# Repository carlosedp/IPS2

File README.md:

# IPS2

The infamous interruptible power supply is back version 2 with usbC and more mmpfh (700mA@12V / 500mA@-12V).

IPS is a 2HP opensource (cc-by-sa-nc) eurorack module. It’s a switched-mode power supply that converts the 5V power from any USB type C interface/charger into +12V/-12V for your modular synthesizer. This does not allow you to power big racks but can easily power up small to medium size systems (check powerconsumption with f.e. modulargrid.net)
You can also use the unit without frontpanel inside a case (no access to the SHUT inputs) if it has a power switch and a 5V input.

Unlike IPS1 this module is built around a monolytic IC which houses two independent regulators, the TPS65131 from TI. It still has the infamous shutdown inputs for the regulators, which are accessible thru two jacks on the frontpanel.
Quote from IPS1: “This gives you a very different approach to operate a connected module. By “proper” modulation of it’s own powersupply voltages any connected module(s) can operate then in a, let’s say:  “near death state”, which can create interesting effects.

DISCLAIMER:
The shutdown inputs are a very experimental feature for those who like to experiment on their own risk with reduced or chopped supply voltages for their modules/setup. We take no responibility for damage or the like. (should not occur, cause no inversion of voltage is possible, only reduction of voltage is possible)

In a glimpse:

- modern and fast 1.25MHz switching regulator from Texas Instruments deliver up to 700mA@12V and 500mA@-12V
- IPS mainboard can be mounted inside a case without frontpanel like a common PSU (flatmount, has 2nd location for USB C connector and also pads for wires)
- cheap – can be used with any USB type C charger
- it’s friggin tiny

In this fork, I've replaced the USB connectors to some more available on JLCPCB.

Also I've added a front-panel design that is connected to the PCB with break-tabs so they can
be easily manufactured in one run and separated. Components also have JLCPCB part numbers.

I/O:

- SHUT +12V deactivates the swiching regulator for the positive rail
- SHUT -12V deactivates the switching regulator for the negative rail
- internal 10 pin molex output header

Power Output:

- +12V 700mA / -12V 500mA (if incoming USB interface delivers it)

Dimensions:

- Width: 2 HP (10mm)
- Depth: 13mm

## License

CC-BY-SA-NC license

by seismic industries / 2019

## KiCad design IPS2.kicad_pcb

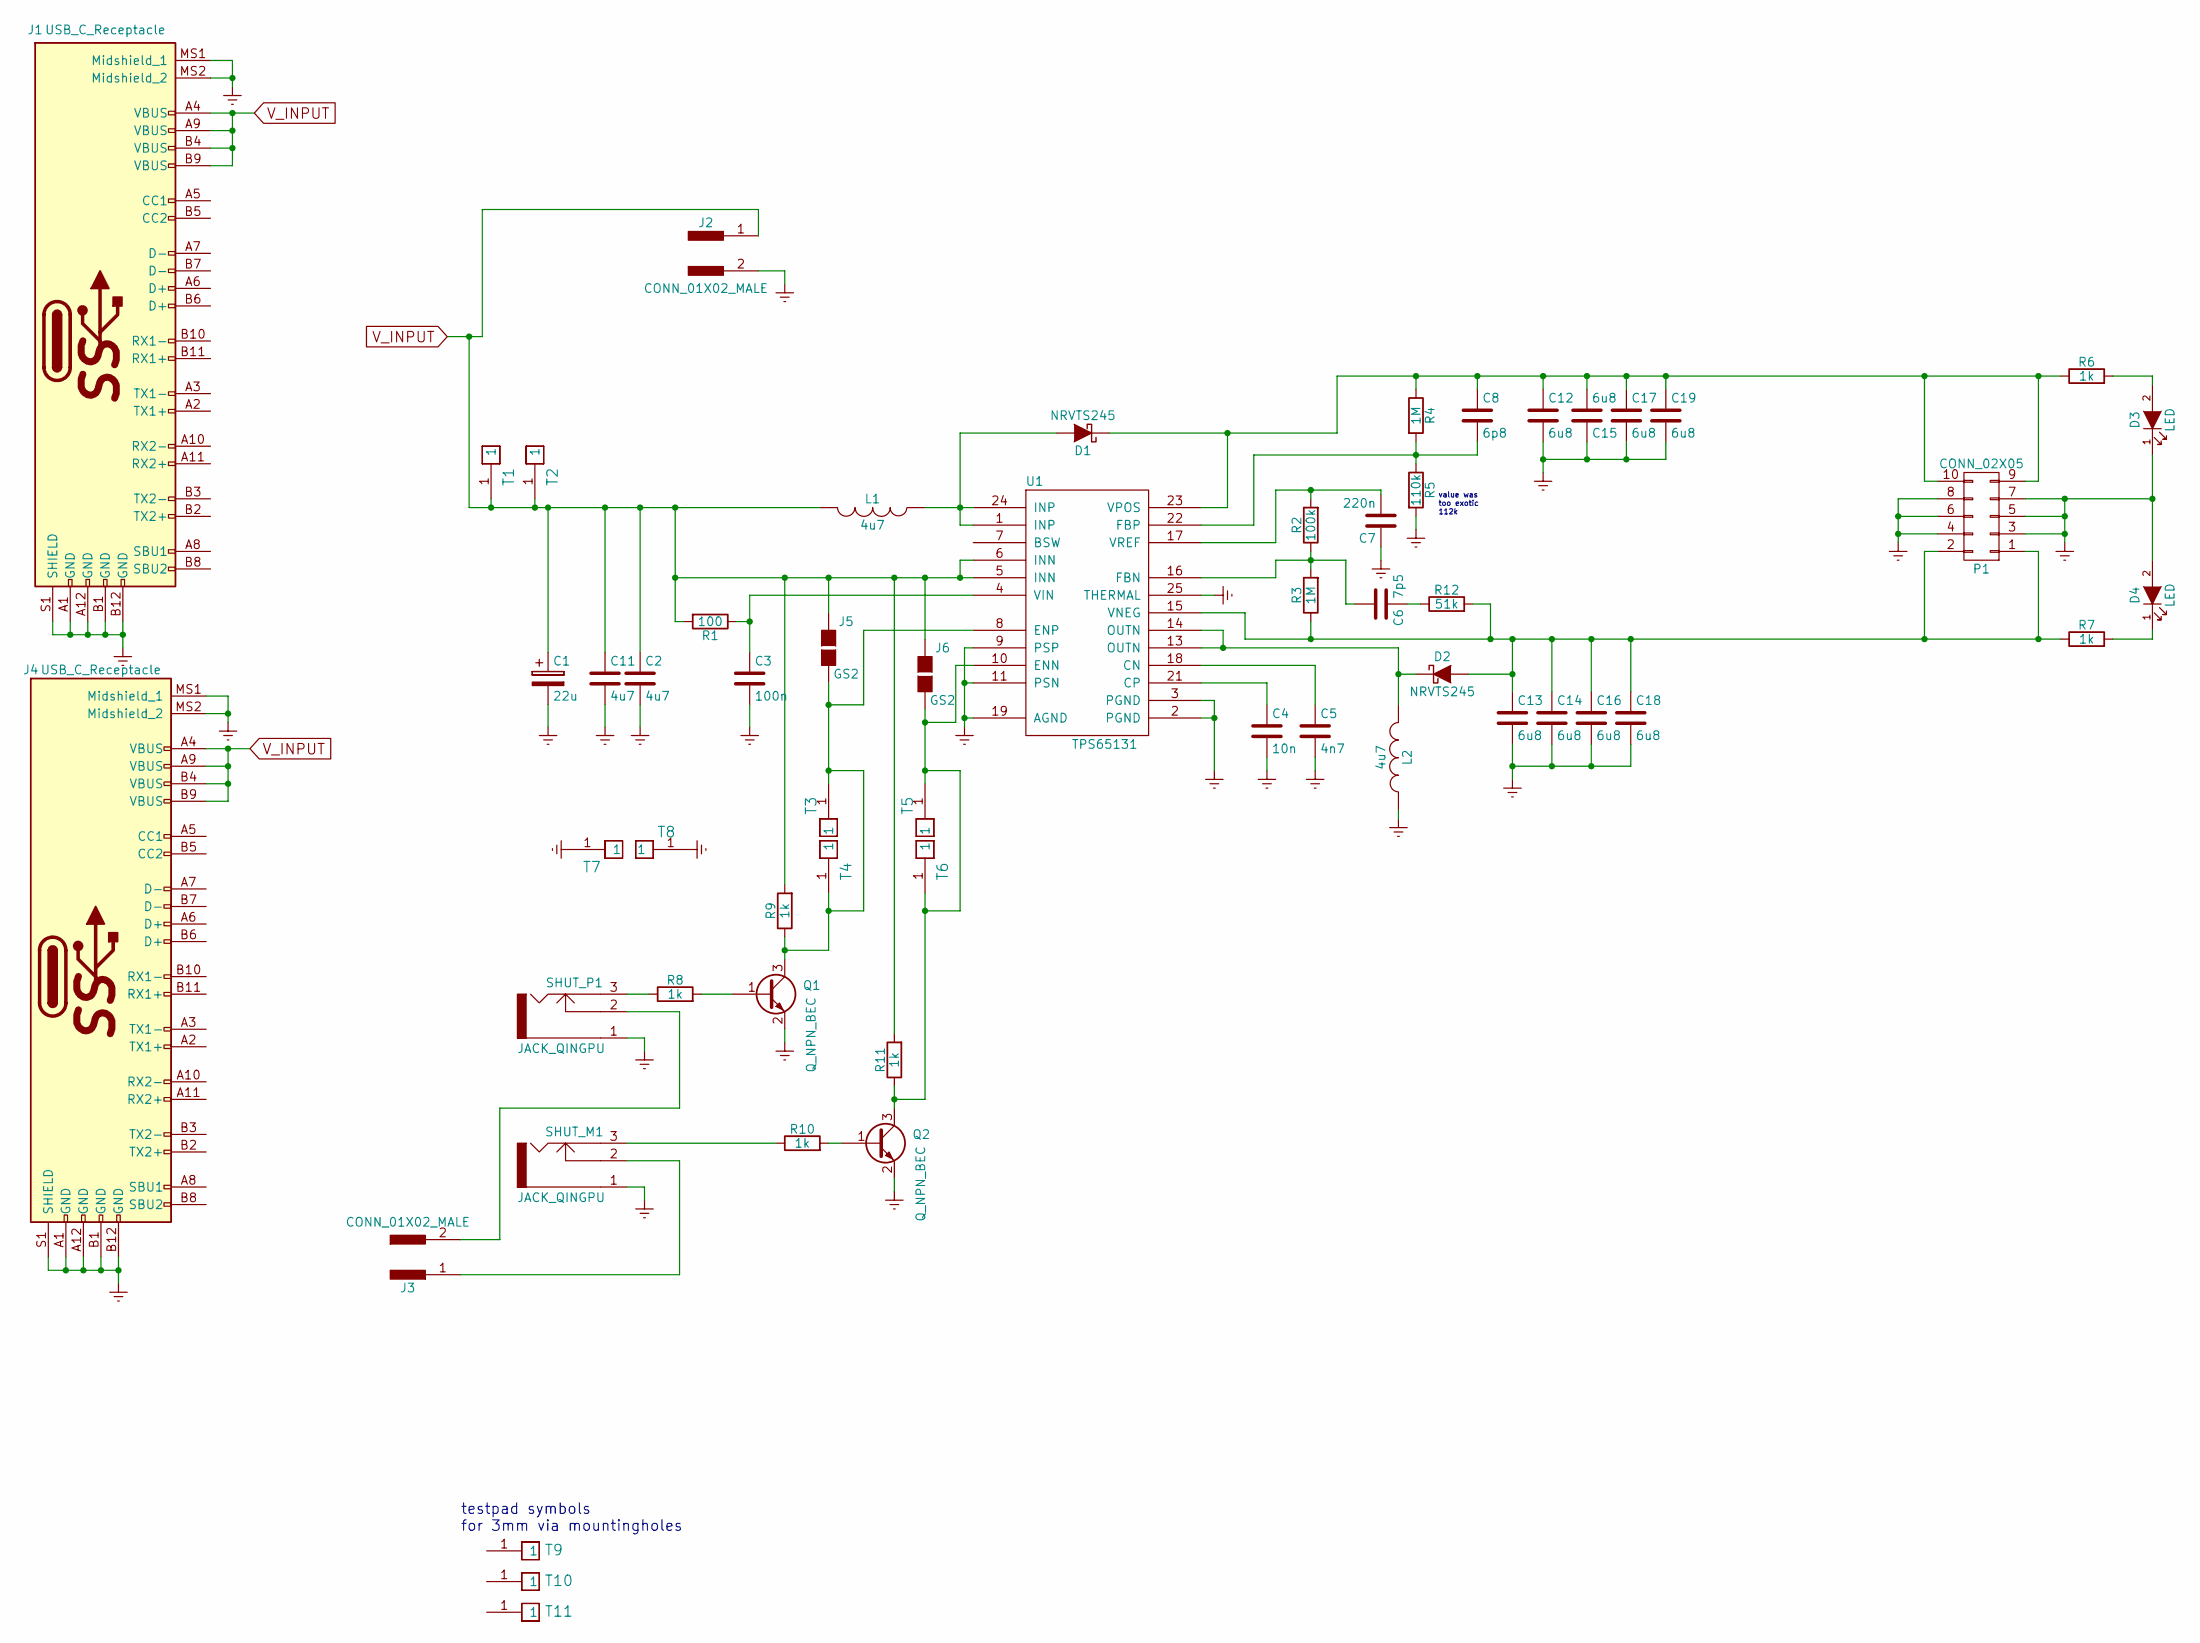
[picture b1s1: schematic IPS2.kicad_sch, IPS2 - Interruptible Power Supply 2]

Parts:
C1: 22u; CP_Elec_7.3x4.3; MPN EEF-CX1D220R; LCSC C465932
C2, C11: 4u7; C_0805; MPN GRM21BR61H475KE51L; LCSC C1779
C3: 100n; C_0603; MPN C0603C104Z3VACTU; LCSC C14663
C4: 10n; C_0603; MPN 885012206065; LCSC C57112
C5: 4n7; C_0603; MPN 885012206087; LCSC C53987
C6: 7p5; C_0603; MPN GRM1885C1H7R5BA1D; LCSC C53424
C7: 220n; C_0603; MPN CC603KRX7R7BB224; LCSC C21120
C8: 6p8; C_0603; MPN 885012006050; LCSC C1679
C12, C13, C14, C15, C16, C17, C18, C19: 6u8; C_1206; MPN C3216X7R1E685K160AB; LCSC C7393982
D1, D2: NRVTS245; D_SOD-123F; MPN NRVTS245ESFT3G; LCSC C154804
D3, D4: LED; C_0805; MPN APT2012SGC; LCSC C5353439
J1, J4: USB_C_Receptacle; USB_TYPE_C_WUERTH_632723300011; MPN 632723300011; LCSC C2988369
J2: CONN_01X02_MALE; Pin_Header_Angled_1x02_Pitch2.54mm
J3: CONN_01X02_MALE; Pin_Header_Angled_2x01_Pitch2.54mm
J5, J6: GS2
L1, L2: 4u7; Inductor_SRN4018TA_bourns; MPN SRN4018TA-4R7M; LCSC C1330726
P1: CONN_02X05; Pin_Header_Angled_2x05_Pitch2.54mm_with_space_for_con; MPN 649-68020-110HLF
Q1, Q2: Q_NPN_BEC; SOT-23; MPN BC847CLT1G; LCSC C150094
R1: 100; R_0603; MPN CRCW0603100RFKEAC; LCSC C22775
R2: 100k; R_0603; MPN RCA0603100KJNEC; LCSC C25803
R3, R4: 1M; R_0603; MPN RC0603FR-071ML; LCSC C22935
R5: 110k; R_0603; MPN CR0603-FX-1103ELF; LCSC C25805
R6, R7, R8, R9, R10, R11: 1k; R_0603; MPN RC0603FR-071KL; LCSC C21190
R12: 51k; R_0603; MPN RC0603FR-0751KL; LCSC C23196
SHUT_M1: JACK_QINGPU; jack_qingpu
SHUT_P1: JACK_QINGPU; jack_qingpu
T1, T2, T3, T4, T5, T6, T7, T8: TESTPIN; TESTPAD_SMD_and_THT_SQR
T9, T10, T11: TESTPIN; VIA_M3_mounting_hole
U1: TPS65131; QFN-24-4x4mm_Pitch0.5mm_handsolder_big_thermal_hole; MPN TPS65131RGER; LCSC C87663

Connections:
Earth: C1.2, C2.2, C3.2, C4.2, C5.2, C7.1, C11.2, C12.2, C13.2, C14.2, C15.1, C16.2, C17.2, C18.2, C19.2, D3.1 (K), D4.2 (A), J1.A1 (GND), J1.A12 (GND), J1.B1 (GND), J1.B12 (GND), J1.MS1 (Midshield_1), J1.MS2 (Midshield_2), J1.S1 (SHIELD), J2.2, J4.A1 (GND), J4.A12 (GND), J4.B1 (GND), J4.B12 (GND), J4.MS1 (Midshield_1), J4.MS2 (Midshield_2), J4.S1 (SHIELD), L2.1, P1.3, P1.4, P1.5, P1.6, P1.7, P1.8, Q1.2 (E), Q2.2 (E), R5.2, SHUT_M1.1, SHUT_P1.1, T7.1, T8.1, U1.2 (PGND), U1.3 (PGND), U1.9 (PSP), U1.11 (PSN), U1.19 (AGND), U1.25 (THERMAL)
unnamed: C3.1, R1.1, U1.4 (VIN)
unnamed: C4.1, U1.21 (CP)
unnamed: C5.1, U1.18 (CN)
unnamed: C6.1, R12.1
unnamed: C6.2, R2.1, R3.2, U1.16 (FBN)
unnamed: C7.2, R2.2, U1.17 (VREF)
unnamed: C8.2, R4.2, R5.1, U1.22 (FBP)
unnamed: C8.1, C12.1, C15.2, C17.1, C19.1, D1.1 (K), P1.9, P1.10, R4.1, R6.1, U1.23 (VPOS)
unnamed: C13.1, C14.1, C16.1, C18.1, D2.2 (A), P1.1, P1.2, R3.1, R7.1, R12.2, U1.15 (VNEG)
unnamed: D1.2 (A), L1.1, U1.1 (INP), U1.24 (INP)
unnamed: D2.1 (K), L2.2, U1.13 (OUTN), U1.14 (OUTN)
unnamed: D3.2 (A), R6.2
unnamed: D4.1 (K), R7.2
unnamed: J3.1, SHUT_M1.2
unnamed: J3.2, SHUT_P1.2
unnamed: J5.2 (G2), Q1.3 (C), R9.1, T3.1, T4.1, U1.8 (ENP)
unnamed: J6.2 (G2), Q2.3 (C), R11.1, T5.1, T6.1, U1.10 (ENN)
unnamed: Q1.1 (B), R8.2
unnamed: Q2.1 (B), R10.2
unnamed: R8.1, SHUT_P1.3
unnamed: R10.1, SHUT_M1.3
V_INPUT: C1.1, C2.1, C11.1, J1.A4 (VBUS), J1.A9 (VBUS), J1.B4 (VBUS), J1.B9 (VBUS), J2.1, J4.A4 (VBUS), J4.A9 (VBUS), J4.B4 (VBUS), J4.B9 (VBUS), J5.1 (G1), J6.1 (G1), L1.2, R1.2, R9.2, R11.2, T1.1, T2.1, U1.5 (INN), U1.6 (INN)

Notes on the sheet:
testpad symbols for 3mm via mountingholes
value was too exotic 112k

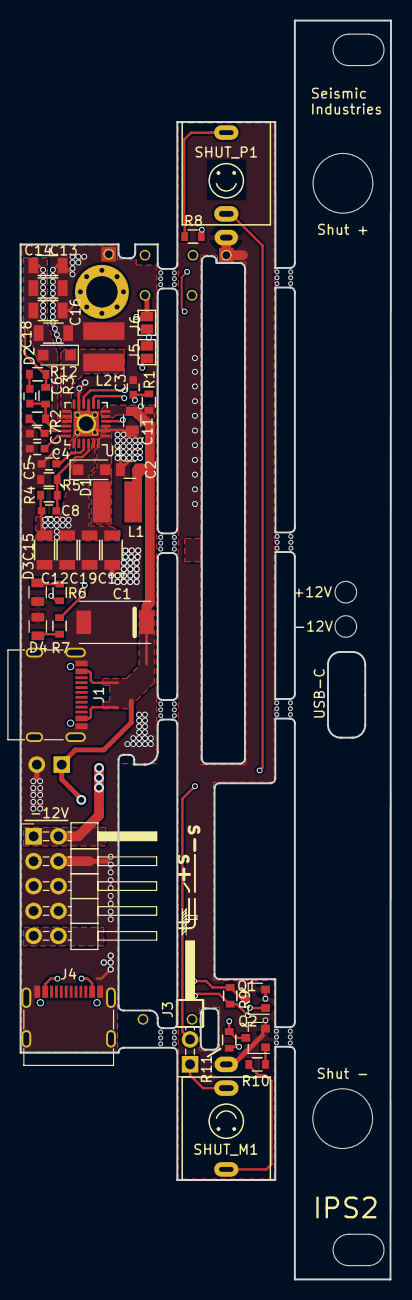
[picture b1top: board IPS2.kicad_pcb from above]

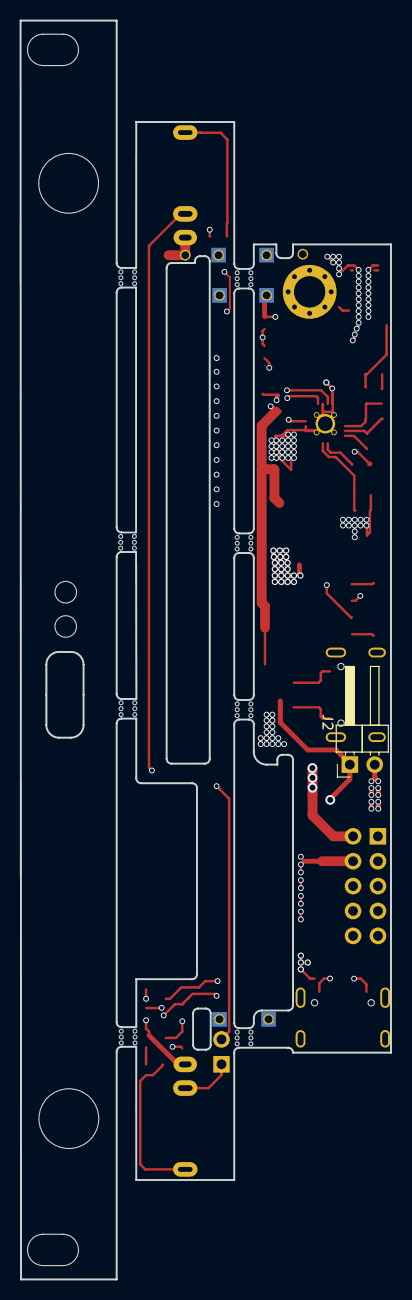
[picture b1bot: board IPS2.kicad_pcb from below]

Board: 2 copper layers, 37.8 x 128.5 mm, 56 parts (7 on the bottom side), 23 nets.

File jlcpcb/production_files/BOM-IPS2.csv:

Comment,Designator,Footprint,LCSC
4u7,"L1,L2",Inductor_SRN4018TA_bourns,C1330726
100n,C3,C_0603,C14663
Q_NPN_BEC,"Q1,Q2",SOT-23,C150094
NRVTS245,"D1,D2",D_SOD-123F,C154804
6p8,C8,C_0603,C1679
4u7,"C11,C2",C_0805,C1779
220n,C7,C_0603,C21120
1k,"R10,R11,R6,R7,R8,R9",R_0603,C21190
100,R1,R_0603,C22775
1M,"R3,R4",R_0603,C22935
51k,R12,R_0603,C23196
100k,R2,R_0603,C25803
110k,R5,R_0603,C25805
USB_C_Receptacle,"J1,J4",USB_C_Receptacle_G-Switch_GT-USB-7010ASV,C2988369
22u,C1,CP_Elec_7.3x4.3,C465932
7p5,C6,C_0603,C53424
LED,"D3,D4",C_0805,C5353439
4n7,C5,C_0603,C53987
10n,C4,C_0603,C57112
6u8,"C12,C13,C14,C15,C16,C17,C18,C19",C_1206,C7393982
TPS65131,U1,QFN-24-4x4mm_Pitch0.5mm_handsolder_big_thermal_hole,C87663

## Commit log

2024-07-16 Update PCB with linked panel with break-tab. Changed USB socket.
2024-07-16 Added JLCPCB parts mapping and Gerbers using Bouni/kicad-jlcpcb-tools plugin
2024-07-16 Add labels to shut jacks. Update readme.
2024-07-16 Clean old files
